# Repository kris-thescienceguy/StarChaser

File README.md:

# Star Chaser: Automatic Dome Controller

The Star Chaser dome control project was led by Kris Turner as part an upgrade, commissioned by Keele Observatory, in order to improve the functionality of their 24" research, reflector telescope.

Keele Observatory is located in North Staffordshire,  between Manchester and Birmingham on a large estate with extensive woods, lakes and parkland, formerly owned by the Sneyd family. 97% of the university's research is classified as world leading and of international importance, as a result of the 2014 Research Excellence Framework (REF 2014).

The software and digital electronics were produced by **Kris Turner**, who at the time of the project, was an undergraduate physics with chemistry student. The mechanical designs were produced by **Dr James Albinson**. **Alan Bagnell** advised on the design, and safety, of the electrical systems.

*A special mention must be made to the entirety of the Keele Observatory volunteers without who there would be no dome to upgrade.*

## Project Overview ##

## Wiring Specifications ##
The system has several parts which may need to replaced over time so for ease of use a wiring colour chart has been produced. This should be used in conjunction with wiring diagrams provided.

### Pulse Switch ###
There is no doubt that the microcontroller will miss some encoder pulses. It may also count some twice. Whether by gain or loss of pulses it’s likely that with extended use and due to cumulative error the accuracy of the system will decrease over time. In order to prevent this, a zero point was chosen where the microcontroller knows the exact azimuth of the dome. Using a magnet on the dome structure and a fixed reed switch, a pulse is sent to the microcontroller when this zero point is reached.

On this interrupt, the microcontroller resets the pulses counted and hence the azimuth of the dome to a known position. This switch is also polled by the driver software as part of the AtHome subroutine.

| Switch Wire | Extended Cable |
| --- | --- |
| Red | Orange |
| Blue | Blue |

### Encoders ###
In order to accurately determine the position of the dome, two incremental encoders are used, although only one is required and currently configurd. Each encoder has four wires: VCC, GND, A Phase, and B Phase. Phase A and phase B are interchangable but will reverse the direction of the encoder. The encoder phase signals require an external pull-up resistor and although the ATTiny25 microcontroller provides internal pull-ups they do not appear to be strong enough.

#### Encoder A ####
| Encoder Function | Encoder Wire | Extended Cable |
| --- | --- | --- |
| VCC | Red | Orange |
| GND | Black | Blue |
| Phase A | Green | Green |
| Phase B | White | Brown |

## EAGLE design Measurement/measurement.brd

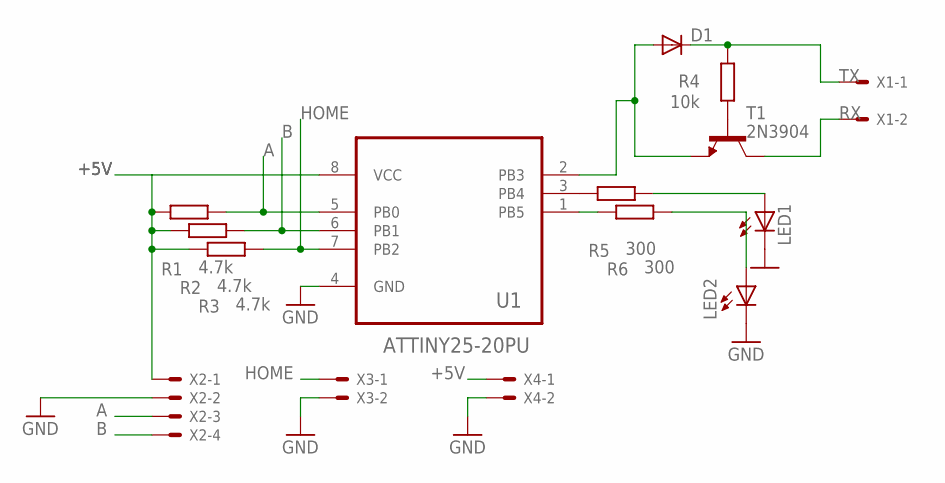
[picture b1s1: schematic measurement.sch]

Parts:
D1: 1N4148DO35-7; DO35-7
LED1, LED2: LED5MM
R1, R2, R3: 4.7k; 0414V
R4: 10k; 0414V
R5, R6: 300; 0414V
T1: 2N3904; TO92
U1: ATTINY25-20PU; DIP254P762X533-8
X1, X3, X4: 5566-2
X2: 5566-4

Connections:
+5V: R1.1, R2.1, R3.1, U1.8 (VCC), X2.1, X4.1
A: R1.2, U1.5 (PB0), X2.3
B: R2.2, U1.6 (PB1), X2.4
GND: LED1.K (C), LED2.K (C), U1.4 (GND), X2.2, X3.2, X4.2
HOME: R3.2, U1.7 (PB2), X3.1
unnamed: R4.1, T1.2 (B)
unnamed: D1.A, T1.3 (E), U1.2 (PB3)
unnamed: R5.1, U1.3 (PB4)
unnamed: LED1.A, R5.2
unnamed: LED2.A, R6.2
unnamed: R6.1, U1.1 (PB5)
RX: T1.1 (C), X1.2
TX: D1.C, R4.2, X1.1

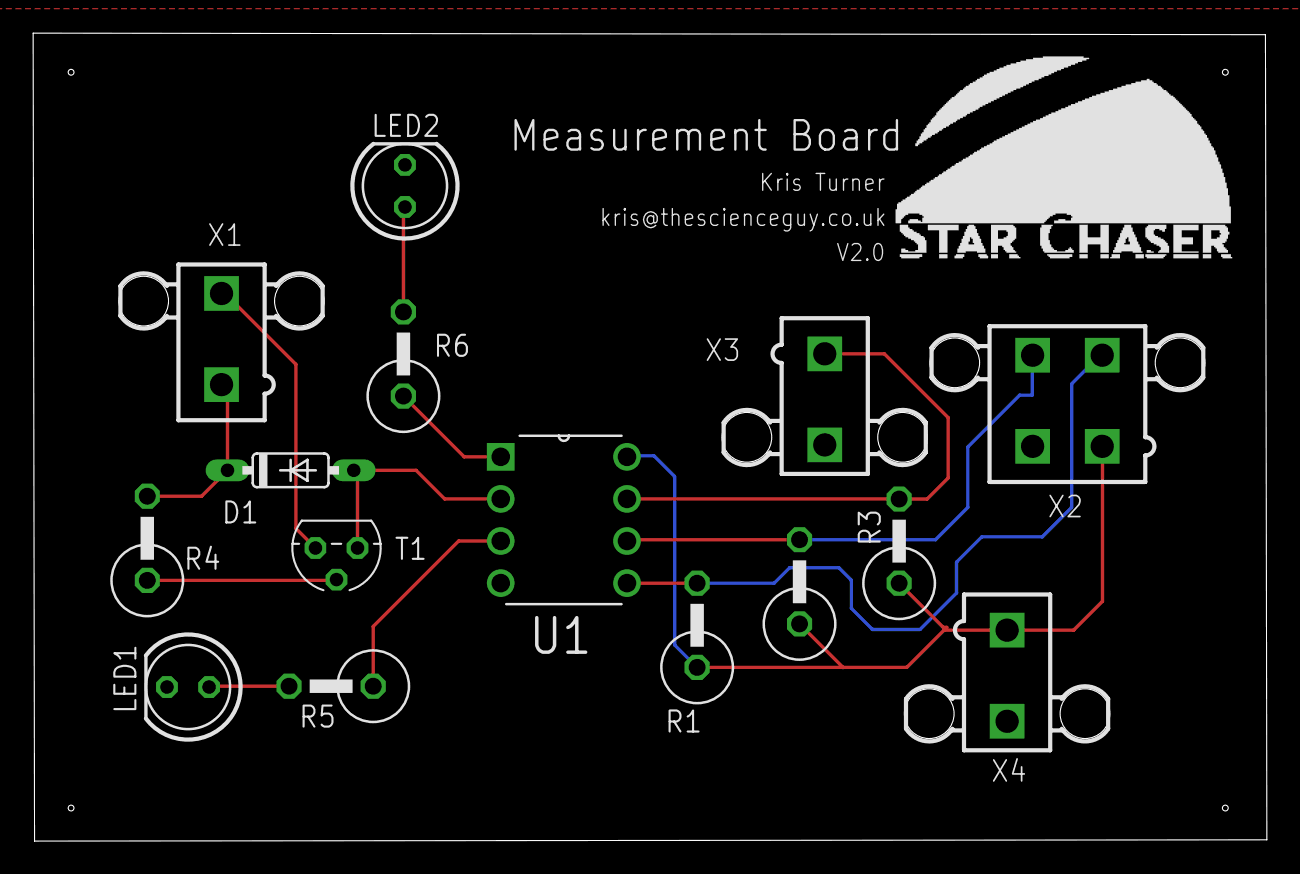
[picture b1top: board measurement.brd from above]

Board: 2 copper layers, 74.5 x 48.8 mm, 15 parts (0 on the bottom side), 13 nets.

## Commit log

2018-12-15 Update README.md
    Updated README to show project description.
2018-12-15 Update README.md
    Wiring specifications were added.
2018-12-15 Added project schematic diagram.
2018-12-15 Added encoder counter circuit.
2018-12-17 Added details regarding to measurement of the encoder pulses.
2018-12-20 Updated measurement circuit and uploaded. Needs reviewing and then ordering.
2018-12-20 Encoder circuit document updated
2018-12-20 Grammar fixed.
